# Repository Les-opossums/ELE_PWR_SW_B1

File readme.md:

# Power Switch Board - B1

## Description
This board serves as a power switch for the robot power supplies. It uses the battery as an input (24 V).
Two discrete inputs control the activation of the outputs: emergency stop (STOP) and on/off (ON).

All outputs are commanded by the ON input, while others are also subject to the STOP. The outputs are listed below.
- ON + STOP:
    - Motors 1, 2, 3, and 4.
    - Other loads (3 connectos), reserved for actuators (moving parts of the robot).
- ON only: Non stop loads (3 connectors), reserved for robot logics.

Every output has a corresponding LED for debug. Motors 1 and 2 are connected to one fuse, Motors 3 and 4 to another one. Both other outputs have reserved fuses.

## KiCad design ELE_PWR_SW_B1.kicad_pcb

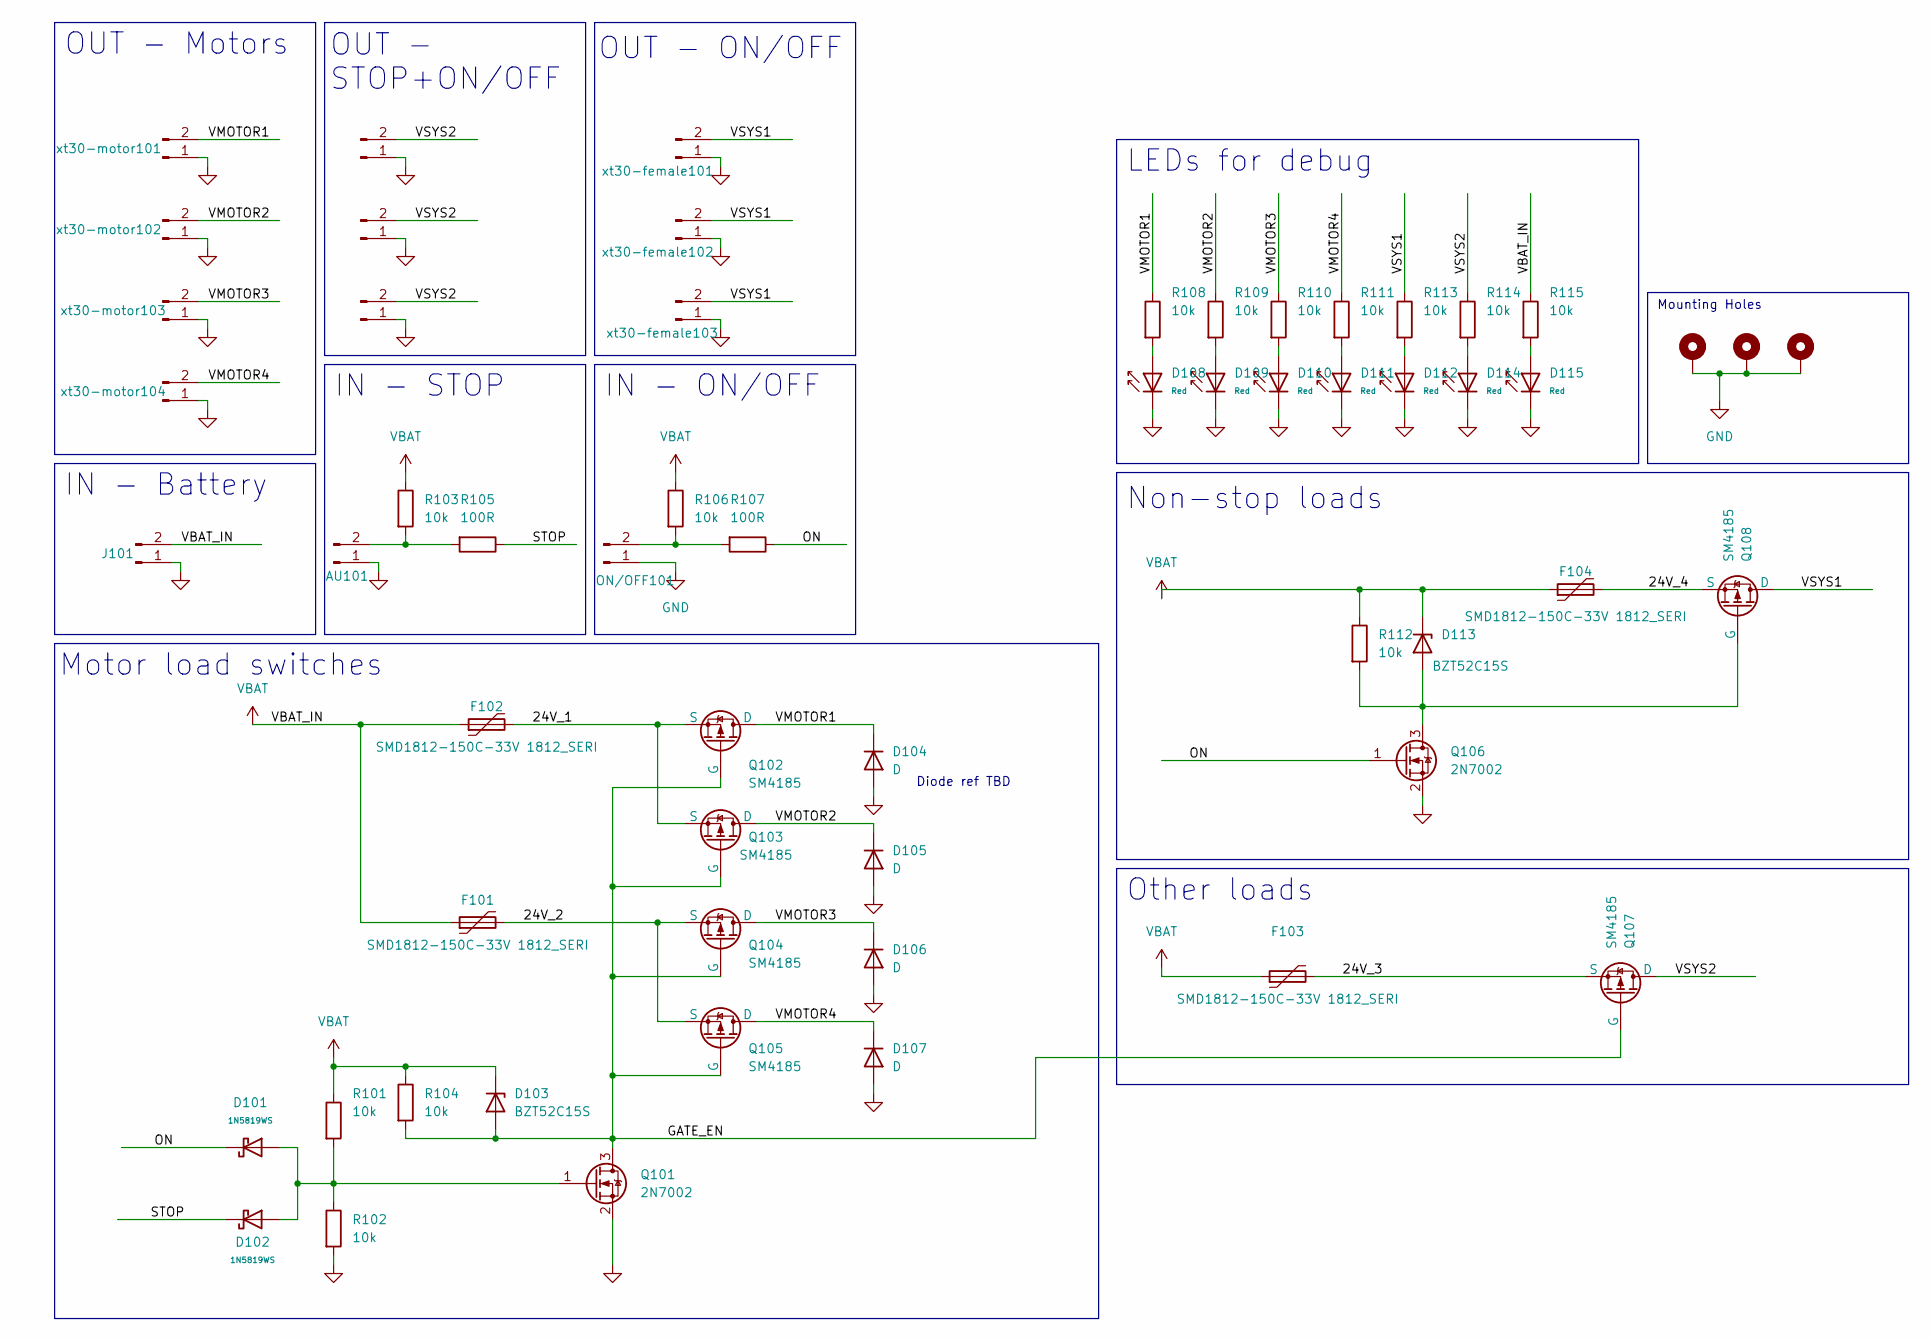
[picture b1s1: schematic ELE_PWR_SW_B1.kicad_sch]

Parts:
AU101: Conn_01x02_Pin; JST_XH_B2B-XH-AM_1x02_P2.50mm_Vertical
D101, D102: 1N5819WS; D_SOD-323; Forward Voltage (Vf@If) 600mV@1A; Reverse Voltage (Vr) 40V; Part 1N5819WS; LCSC C191023
D103, D113: BZT52C15S; D_SOD-323
D104, D105, D106, D107: D; D_SMA
D108, D109, D110, D111, D112, D114, D115: Red; D_0603; Part KT-0603R; LCSC C2286
F101, F102, F103, F104: SMD1812-150C-33V 1812_SERI; Fuse_Bourns_MF-SM_7.98x5.44mm
H101, H102, H103: MountingHole_Pad; MountingHole_3.2mm_M3_DIN965_Pad
J101: Conn_01x02_Pin; AMASS_XT60-M_1x02_P7.20mm_Vertical
ON/OFF101: Conn_01x02_Pin; JST_XH_B2B-XH-AM_1x02_P2.50mm_Vertical
Q101, Q106: 2N7002; SOT-23
Q102, Q103, Q104, Q105, Q107, Q108: SM4185; TO-252-2
R101, R102, R103, R104, R106, R108, R109, R110, R111, R112, R113, R114, R115: 10k; R_0805_2012Metric_Pad1.20x1.40mm_HandSolder
R105, R107: 100R; R_0805_2012Metric_Pad1.20x1.40mm_HandSolder
xt30-female101, xt30-female102, xt30-female103, xt30-motor101, xt30-motor102, xt30-motor103, xt30-motor104, xt30-motor105, xt30-motor106, xt30-motor107: Conn_01x02_Pin; AMASS_XT30U-F_1x02_P5.0mm_Vertical

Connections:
/24V_1: F102.2, Q102.3 (S), Q103.3 (S)
/24V_2: F101.2, Q104.3 (S), Q105.3 (S)
/24V_3: F103.2, Q107.3 (S)
/24V_4: F104.2, Q108.3 (S)
/GATE_EN: D103.2 (A), Q101.3 (D), Q102.1 (G), Q103.1 (G), Q104.1 (G), Q105.1 (G), Q107.1 (G), R104.2
/ON: D101.1, Q106.1 (G), R107.1
/STOP: D102.1, R105.1
/VMOTOR1: D104.1 (K), Q102.2 (D), R108.1, xt30-motor101.2
/VMOTOR2: D105.1 (K), Q103.2 (D), R109.1, xt30-motor102.2
/VMOTOR3: D106.1 (K), Q104.2 (D), R110.1, xt30-motor103.2
/VMOTOR4: D107.1 (K), Q105.2 (D), R111.1, xt30-motor104.2
/VSYS1: Q108.2 (D), R113.1, xt30-female101.2, xt30-female102.2, xt30-female103.2
/VSYS2: Q107.2 (D), R114.1, xt30-motor105.2, xt30-motor106.2, xt30-motor107.2
GND: AU101.1, D104.2 (A), D105.2 (A), D106.2 (A), D107.2 (A), D108.1, D109.1, D110.1, D111.1, D112.1, D114.1, D115.1, H101.1, H102.1, H103.1, J101.1, ON/OFF101.1, Q101.2 (S), Q106.2 (S), R102.2, xt30-female101.1, xt30-female102.1, xt30-female103.1, xt30-motor101.1, xt30-motor102.1, xt30-motor103.1, xt30-motor104.1, xt30-motor105.1, xt30-motor106.1, xt30-motor107.1
unnamed: AU101.2, R103.2, R105.2
unnamed: D108.2, R108.2
unnamed: D109.2, R109.2
unnamed: D110.2, R110.2
unnamed: D111.2, R111.2
unnamed: D112.2, R113.2
unnamed: D113.2 (A), Q106.3 (D), Q108.1 (G), R112.2
unnamed: D114.2, R114.2
unnamed: D115.2, R115.2
unnamed: ON/OFF101.2, R106.2, R107.2
unnamed: D101.2, D102.2, Q101.1 (G), R101.2, R102.1
VBAT: D103.1 (K), D113.1 (K), F101.1, F102.1, F103.1, F104.1, J101.2, R101.1, R103.1, R104.1, R106.1, R112.1, R115.1

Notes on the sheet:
OUT - STOP+ON/OFF
OUT - Motors
OUT - ON/OFF
IN - STOP
Motor load switches
IN - Battery
LEDs for debug
Mounting Holes
Diode ref TBD
Other loads
IN - ON/OFF
Non-stop loads

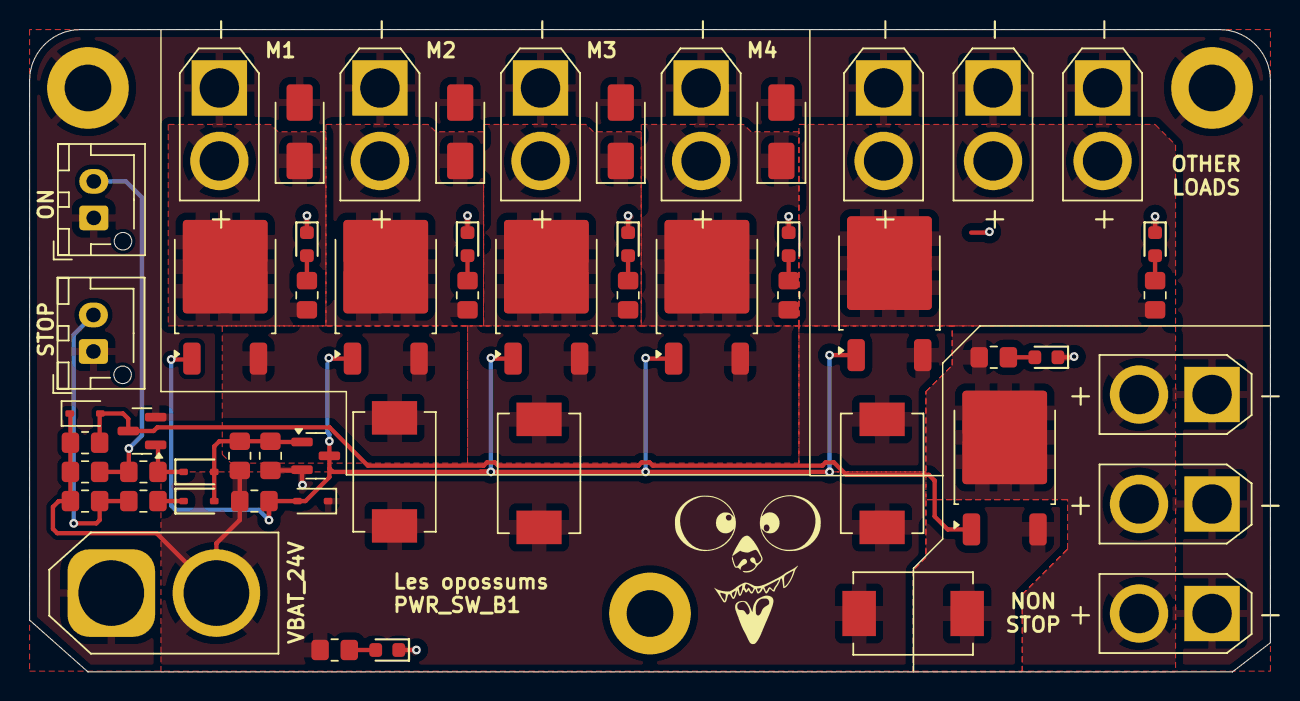
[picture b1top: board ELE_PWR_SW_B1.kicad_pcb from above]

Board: 2 copper layers, 85.0 x 44.0 mm, 58 parts (0 on the bottom side), 26 nets.

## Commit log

2025-11-15 Finish board
